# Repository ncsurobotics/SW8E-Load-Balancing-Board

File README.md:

# Load-Balancing-Board
This repo contains the design files and other relevant information about the load balancing board for SW8.

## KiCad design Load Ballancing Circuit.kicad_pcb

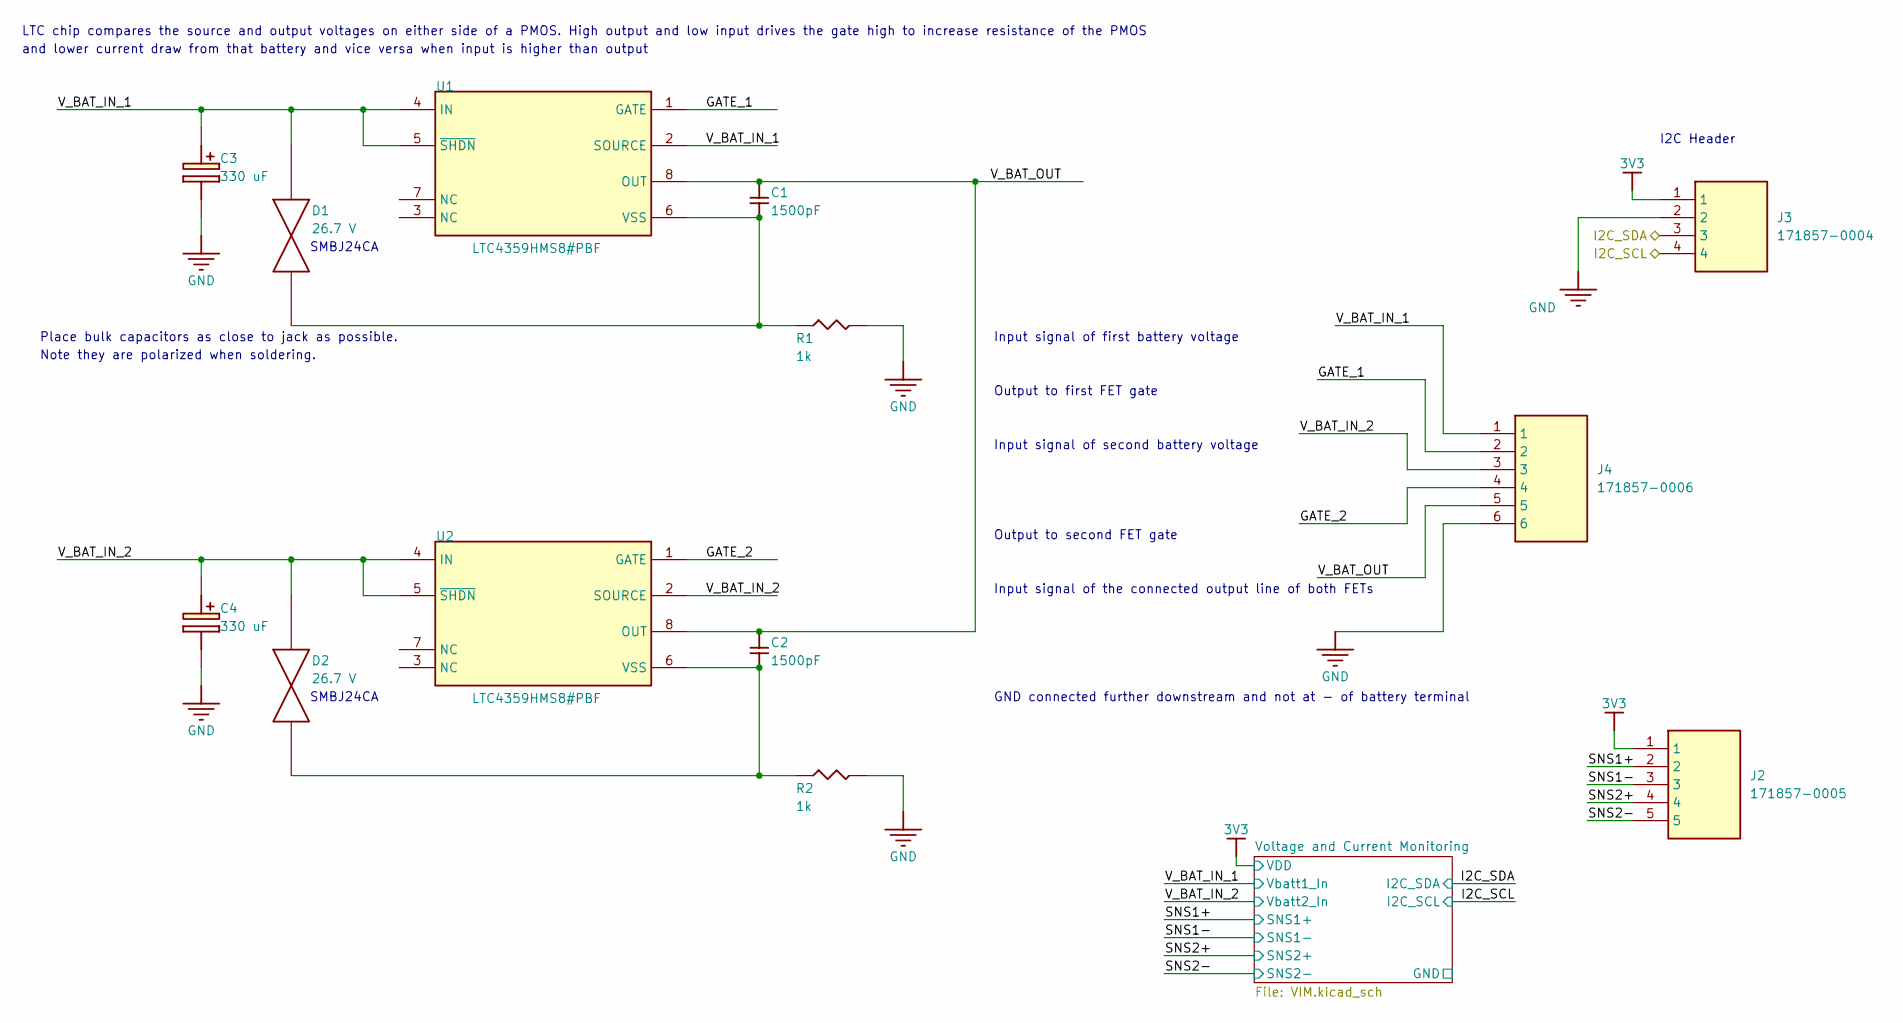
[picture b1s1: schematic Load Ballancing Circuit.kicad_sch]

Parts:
C1, C2: 1500pF; SMD-0805C; Part Number GRM216R71H152KA01D
C3, C4: 330 uF; CAPPRD350W65D800H2200; Part Number EEU-FM1V331LB
D1, D2: 26.7 V; Zenor Diode - duplicate; Part Number SMBJ24CA
J2: 171857-0005; 1718570005; Manufacturer_Part_Number 171857-0004; Mouser Part Number 538-171857-0004
J3: 171857-0004; 1718570004; Manufacturer_Part_Number 171857-0004; Mouser Part Number 538-171857-0004
J4: 171857-0006; 1718570006; Manufacturer_Part_Number 171857-0004; Mouser Part Number 538-171857-0004
R1, R2: 1k; SMD-0805-RES; Part Number ERJ-P06F1001V
U1, U2: LTC4359HMS8#PBF; FP-MS8-8-05-08-1660-IPC_A; Part Number LTC4359HMS8#PBF

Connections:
3V3: J2.1, J3.1; also elsewhere on the board
/GATE_1: J4.2, U1.1 (GATE)
/GATE_2: J4.4, U2.1 (GATE)
/I2C_SCL: J3.4; also elsewhere on the board
/I2C_SDA: J3.3; also elsewhere on the board
/SNS1+: J2.2; also elsewhere on the board
/SNS1-: J2.3; also elsewhere on the board
/SNS2+: J2.4; also elsewhere on the board
/SNS2-: J2.5; also elsewhere on the board
/V_BAT_IN_1: C3.1 (+), D1.A, J4.1, U1.2 (SOURCE), U1.4 (IN), U1.5 (~SHDN); also elsewhere on the board
/V_BAT_IN_2: C4.1 (+), D2.A, J4.3, U2.2 (SOURCE), U2.4 (IN), U2.5 (~SHDN); also elsewhere on the board
/V_BAT_OUT: C1.1, C2.1, J4.5, U1.8 (OUT), U2.8 (OUT)
GND: C3.2 (-), C4.2 (-), J3.2, J4.6, R1.2, R2.2; also elsewhere on the board
unnamed: C1.2, D1.K (2), R1.1, U1.6 (VSS)
unnamed: C2.2, D2.K (2), R2.1, U2.6 (VSS)

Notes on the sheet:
LTC chip compares the source and output voltages on either side of a PMOS. High output and low input drives the gate high to increase resistance of the PMOS
Output to second FET gate
GND connected further downstream and not at - of battery terminal
Input signal of first battery voltage
Output to first FET gate
Note they are polarized when soldering.
and lower current draw from that battery and vice versa when input is higher than output
Input signal of second battery voltage
I2C Header
Input signal of the connected output line of both FETs
SMBJ24CA
Place bulk capacitors as close to jack as possible.

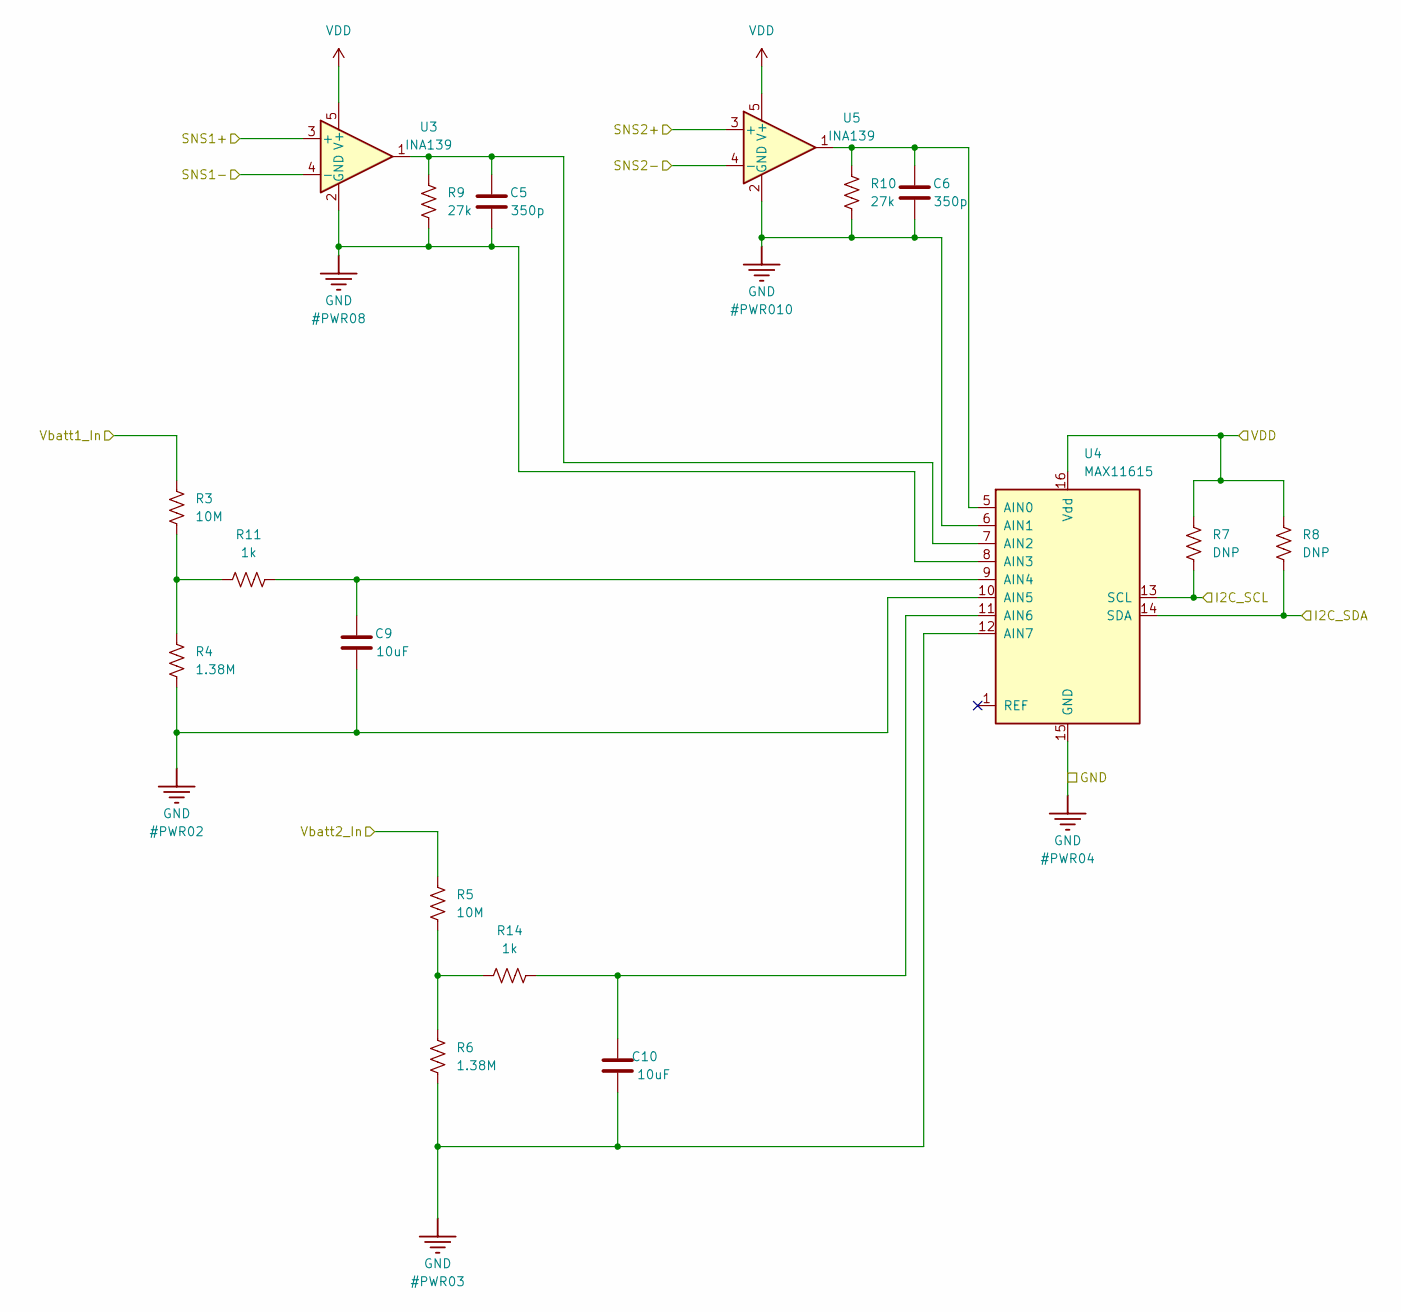
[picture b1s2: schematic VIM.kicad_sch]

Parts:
C5, C6: 350p; C_0805_2012Metric_Pad1.18x1.45mm_HandSolder
C9, C10: 10uF; C_0805_2012Metric_Pad1.18x1.45mm_HandSolder
R3, R5: 10M; R_0805_2012Metric_Pad1.20x1.40mm_HandSolder
R4, R6: 1.38M; R_0805_2012Metric_Pad1.20x1.40mm_HandSolder
R7, R8: DNP; R_0805_2012Metric_Pad1.20x1.40mm_HandSolder
R9, R10: 27k; R_0805_2012Metric_Pad1.20x1.40mm_HandSolder
R11, R14: 1k; R_0805_2012Metric_Pad1.20x1.40mm_HandSolder
U3, U5: INA139; SOT-23-5
U4: MAX11615; QSOP-16_3.9x4.9mm_P0.635mm

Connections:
3V3: R7.2, R8.2, U3.5 (V+), U4.16 (Vdd), U5.5 (V+); also elsewhere on the board
/I2C_SCL: R7.1, U4.13 (SCL); also elsewhere on the board
/I2C_SDA: R8.1, U4.14 (SDA); also elsewhere on the board
/SNS1+: U3.3 (+); also elsewhere on the board
/SNS1-: U3.4 (-); also elsewhere on the board
/SNS2+: U5.3 (+); also elsewhere on the board
/SNS2-: U5.4 (-); also elsewhere on the board
/V_BAT_IN_1: R3.2; also elsewhere on the board
/V_BAT_IN_2: R5.2; also elsewhere on the board
GND: C5.1, C6.1, C9.1, C10.1, R4.2, R6.2, R9.1, R10.1, U3.2 (GND), U4.6 (AIN1), U4.8 (AIN3), U4.10 (AIN5), U4.12 (AIN7), U4.15 (GND), U5.2 (GND); also elsewhere on the board
unnamed: R3.1, R4.1, R11.2
unnamed: R5.1, R6.1, R14.2
unnamed: C6.2, R10.2, U4.5 (AIN0), U5.1
unnamed: C5.2, R9.2, U3.1, U4.7 (AIN2)
unnamed: C9.2, R11.1, U4.9 (AIN4)
unnamed: C10.2, R14.1, U4.11 (AIN6)

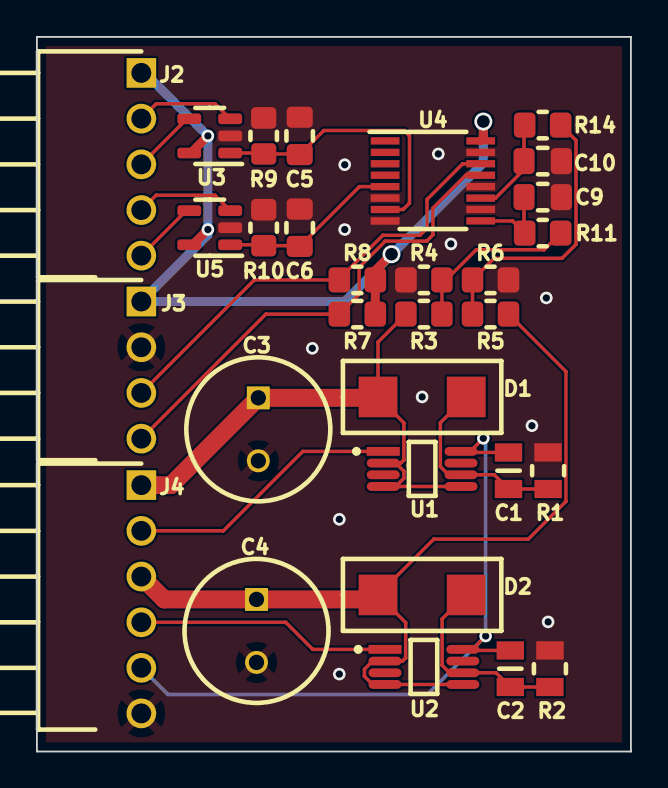
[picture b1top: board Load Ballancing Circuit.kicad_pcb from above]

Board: 2 copper layers, 33.0 x 39.7 mm, 30 parts (0 on the bottom side), 21 nets.

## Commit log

2020-07-31 Create LICENSE
    Add MIT license.
2020-09-02 initial commit Altium
2021-05-29 Libraries partially updated
2021-05-31 Schematic nets and libraries updated, missing large capacitor part number
2021-06-02 replaced IC boward with proper footprint
2021-06-05 PCB completed. Only design rule errors from library footprints
2021-06-09 Schematic complete, PCB routed but needs logos
2021-06-12 DFM submitted
2021-06-22 GIFs added
2022-02-03 added Marcus's .gitignore
2023-04-12 Imported MSB to KiCad
2023-07-04 File structure and gitignore cleanup
2023-07-04 Fix footprint and drc issues
2023-07-04 Remove imported symbol table fields
2023-07-04 Update board settings from template
2023-09-27 V and I Monitoring Module
2023-09-27 Pushed schematic for module
2023-10-13 Added some ports
2023-10-19 added connectors and did layout
2023-10-19 board is now now a weird size
2023-10-21 added rc lp and cm filter to vdiv
2023-10-24 changed circuit
2023-10-24 fixed drc issues
2023-10-25 removed comic-sans
2023-11-02 changed v-divider
2023-11-02 contemplated life and then changed it again
